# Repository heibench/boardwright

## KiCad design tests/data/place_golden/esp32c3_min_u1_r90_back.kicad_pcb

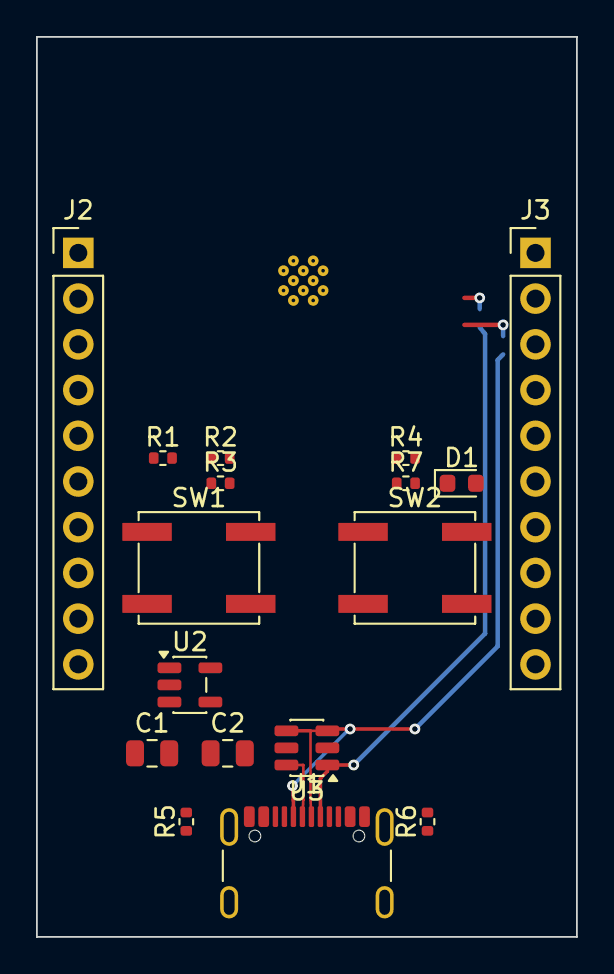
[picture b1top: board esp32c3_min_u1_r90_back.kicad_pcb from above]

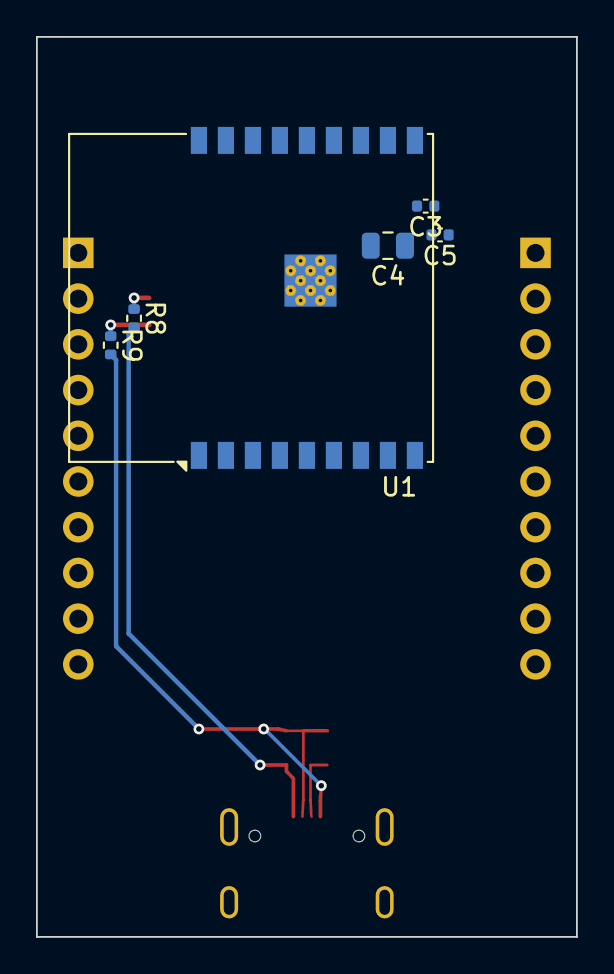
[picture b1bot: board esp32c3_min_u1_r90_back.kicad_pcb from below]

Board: 2 copper layers, 30.0 x 50.0 mm, 23 parts (6 on the bottom side), 24 nets.

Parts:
C1, C2, C4: 10u; C_0805_2012Metric
C3: 100n; C_0402_1005Metric
C5: 1u; C_0402_1005Metric
D1: IO7; LED_0603_1608Metric
J1: USB-C; USB_C_Receptacle_GCT_USB4105-xx-A_16P_TopMnt_Horizontal
J2: LEFT; PinHeader_1x10_P2.54mm_Vertical
J3: RIGHT; PinHeader_1x10_P2.54mm_Vertical
R1, R2, R3, R4: 10k; R_0402_1005Metric
R5, R6: 5.1k; R_0402_1005Metric
R7: 1k; R_0402_1005Metric
R8, R9: 22; R_0402_1005Metric
SW1: BOOT; SW_SPST_EVQP0
SW2: RESET; SW_SPST_EVQP0
U1: ESP32-C3-WROOM-02
U2: AP2112K-3.3; SOT-23-5
U3: USBLC6-2SC6; SOT-23-6

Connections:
+3V3: C2.1, C3.1, C4.1, J2.2, J3.9, R1.1, R2.1, R3.1, R4.1, U1.1, U2.5
CC1: J1.A5, R5.1
CC2: J1.B5, R6.1
EN: C5.1, J2.3, R1.2, SW2.1, U1.2
GND: C1.2, C2.2, C3.2, C4.2, C5.2, D1.1, J1.A1, J1.A12, J1.B1, J1.B12, J1.SH, J2.10, J3.1, J3.10, R5.2, R6.2, SW1.2, SW2.2, U1.9, U1.19, U2.2, U3.2
IO0: J3.2, U1.18
IO1: J3.3, U1.17
IO2: J3.4, R4.2, U1.16
IO3: J3.5, U1.15
IO4: J2.4, U1.3
IO5: J2.5, U1.4
IO6: J2.6, U1.5
IO7: J2.7, R7.1, U1.6
IO8: J2.8, R3.2, U1.7
IO9: J2.9, R2.2, SW1.1, U1.8
IO10: J3.6, U1.10
IO20: J3.7, U1.11
IO21: J3.8, U1.12
LED_A: D1.2, R7.2
USB_DM: J1.A7, J1.B7, R9.2, U3.3, U3.4
USB_DM_M: R9.1, U1.13
USB_DP: J1.A6, J1.B6, R8.2, U3.1, U3.6
USB_DP_M: R8.1, U1.14
VBUS: C1.1, J1.A4, J1.A9, J1.B4, J1.B9, J2.1, U2.1, U2.3, U3.5

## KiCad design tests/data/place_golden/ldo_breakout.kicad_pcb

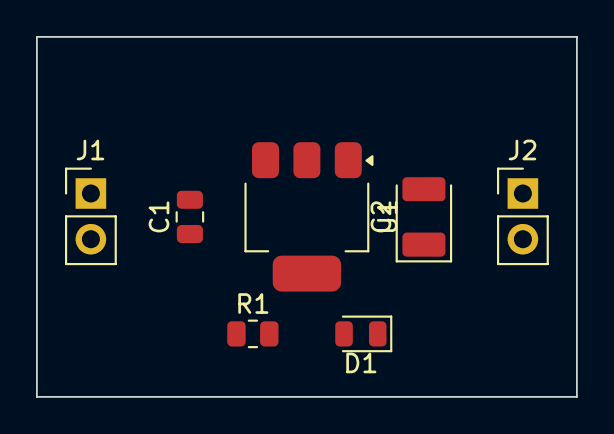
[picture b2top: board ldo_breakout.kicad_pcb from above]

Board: 2 copper layers, 30.0 x 20.0 mm, 7 parts (0 on the bottom side), 4 nets, no tracks yet.

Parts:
C1: 10u; C_0805_2012Metric
C2: 22u tantalum; CP_EIA-3528-21_Kemet-B
D1: green; LED_0805_2012Metric
J1: VIN; PinHeader_1x02_P2.54mm_Vertical
J2: 3V3; PinHeader_1x02_P2.54mm_Vertical
R1: 1k; R_0805_2012Metric
U1: AMS1117-3.3; SOT-223-3_TabPin2

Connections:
+3V3: C2.1, J2.1, R1.1, U1.2
GND: C1.2, C2.2, D1.1, J1.2, J2.2, U1.1
LED_A: D1.2, R1.2
VIN: C1.1, J1.1, U1.3

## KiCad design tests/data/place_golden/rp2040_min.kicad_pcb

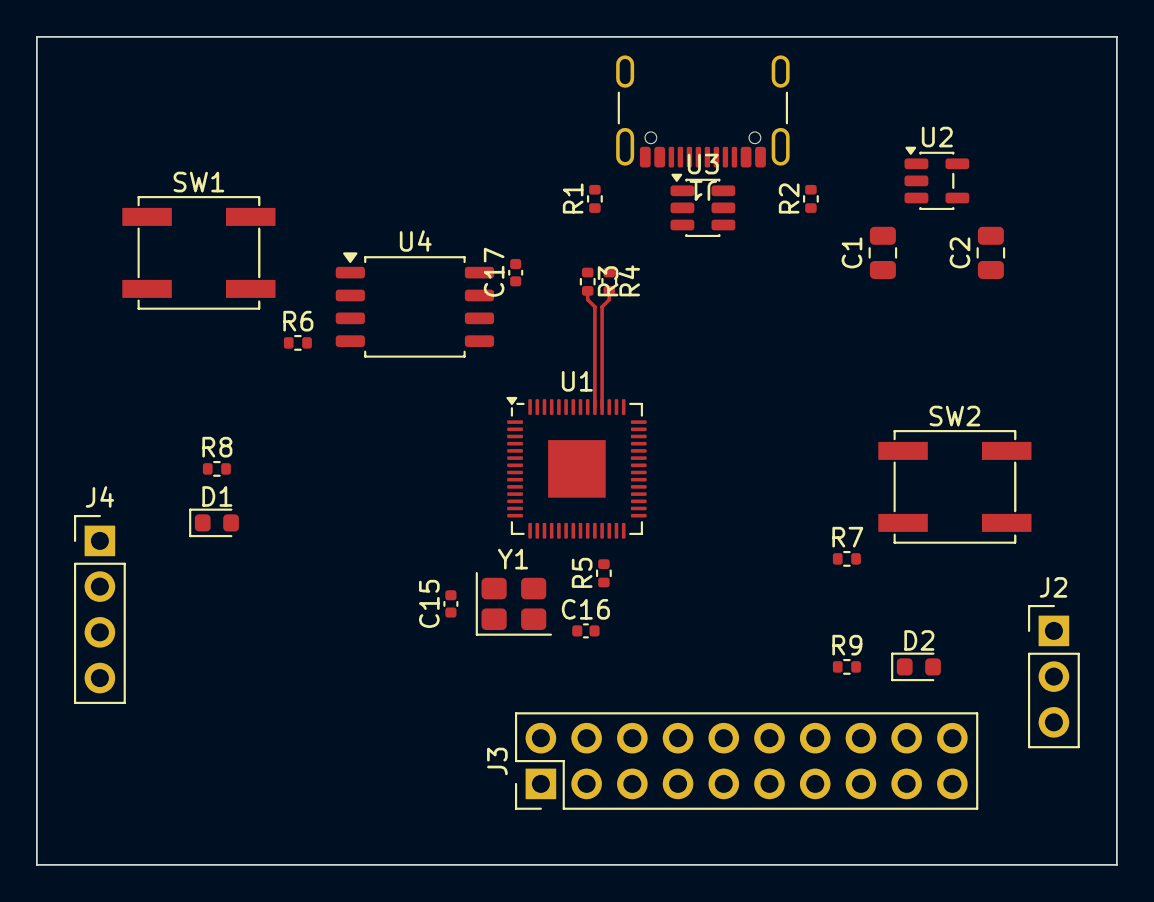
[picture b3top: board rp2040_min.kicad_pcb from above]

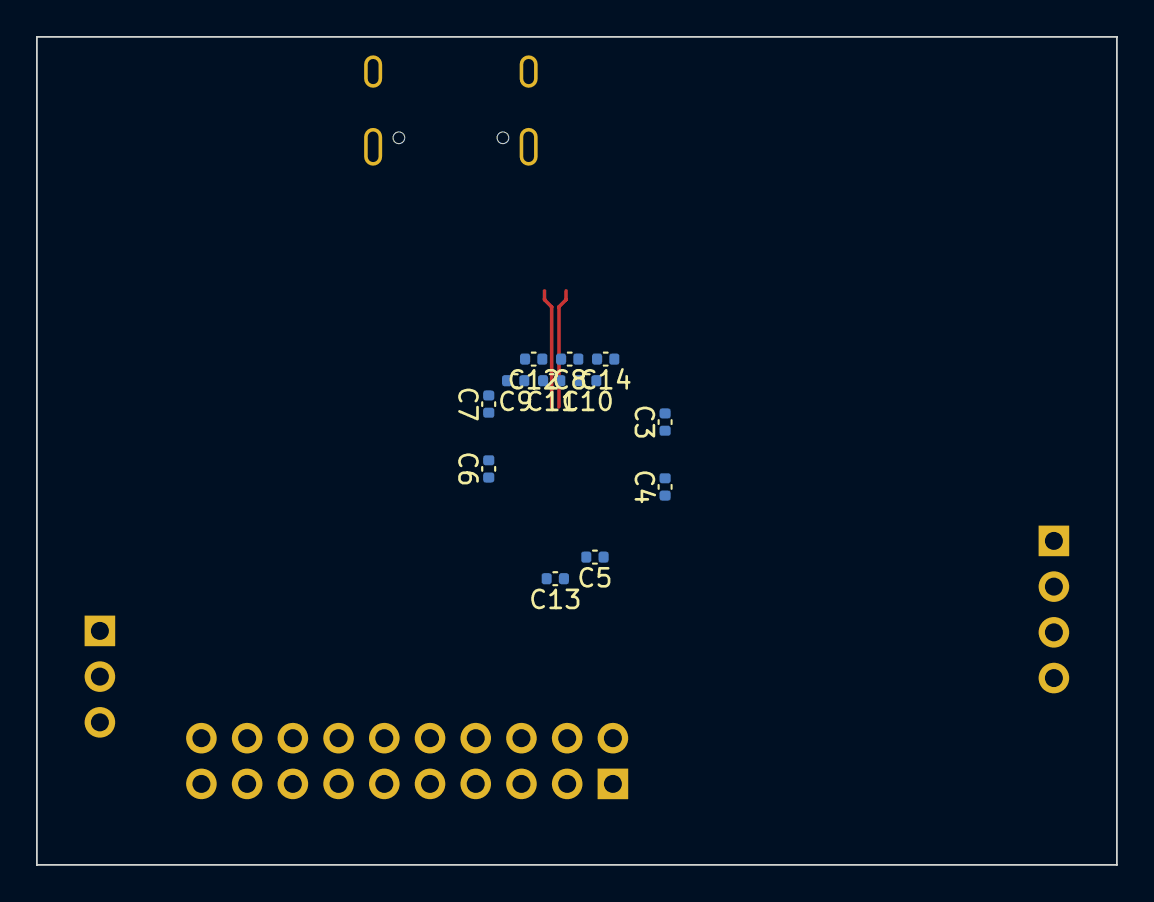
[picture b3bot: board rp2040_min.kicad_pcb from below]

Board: 2 copper layers, 60.0 x 46.0 mm, 39 parts (12 on the bottom side), 46 nets.

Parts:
C1, C2: 10u; C_0805_2012Metric
C3, C4, C5, C6, C7, C8, C9, C10, C13, C14, C17: 100n; C_0402_1005Metric
C11, C12: 1u; C_0402_1005Metric
C15, C16: 15p; C_0402_1005Metric
D1: PWR; LED_0603_1608Metric
D2: GP25; LED_0603_1608Metric
J1: USB-C; USB_C_Receptacle_GCT_USB4105-xx-A_16P_TopMnt_Horizontal
J2: SWD; PinHeader_1x03_P2.54mm_Vertical
J3: GPIO; PinHeader_2x10_P2.54mm_Vertical
J4: PWR; PinHeader_1x04_P2.54mm_Vertical
R1, R2: 5.1k; R_0402_1005Metric
R3, R4: 27; R_0402_1005Metric
R5, R6, R8, R9: 1k; R_0402_1005Metric
R7: 10k; R_0402_1005Metric
SW1: BOOTSEL; SW_SPST_EVQP0
SW2: RESET; SW_SPST_EVQP0
U1: RP2040; QFN-56-1EP_7x7mm_P0.4mm_EP3.2x3.2mm
U2: AP2112K-3.3; SOT-23-5
U3: USBLC6-2SC6; SOT-23-6
U4: W25Q128JVS; SOIC-8_5.3x5.3mm_P1.27mm
Y1: 12MHz; Crystal_SMD_3225-4Pin_3.2x2.5mm

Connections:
+1V1: C12.1, C13.1, C14.1, U1.23, U1.45, U1.50
+3V3: C2.1, C3.1, C4.1, C5.1, C6.1, C7.1, C8.1, C9.1, C10.1, C11.1, C17.1, J4.2, R7.1, R8.1, U1.1, U1.10, U1.22, U1.33, U1.42, U1.43, U1.44, U1.48, U1.49, U2.5, U4.8
BOOT: R6.2, SW1.1
CC1: J1.A5, R1.1
CC2: J1.B5, R2.1
GND: C1.2, C2.2, C3.2, C4.2, C5.2, C6.2, C7.2, C8.2, C9.2, C10.2, C11.2, C12.2, C13.2, C14.2, C15.2, C16.2, C17.2, D1.1, D2.1, J1.A1, J1.A12, J1.B1, J1.B12, J1.SH, J2.2, J4.3, J4.4, R1.2, R2.2, SW1.2, SW2.2, U1.19, U1.57, U2.2, U3.2, U4.4, Y1.2, Y1.4
GPIO0: J3.1, U1.2
GPIO1: J3.2, U1.3
GPIO2: J3.3, U1.4
GPIO3: J3.4, U1.5
GPIO4: J3.5, U1.6
GPIO5: J3.6, U1.7
GPIO6: J3.7, U1.8
GPIO7: J3.8, U1.9
GPIO8: J3.9, U1.11
GPIO9: J3.10, U1.12
GPIO10: J3.11, U1.13
GPIO11: J3.12, U1.14
GPIO12: J3.13, U1.15
GPIO13: J3.14, U1.16
GPIO14: J3.15, U1.17
GPIO15: J3.16, U1.18
GPIO25: R9.1, U1.37
GPIO26: J3.17, U1.38
GPIO27: J3.18, U1.39
GPIO28: J3.19, U1.40
GPIO29: J3.20, U1.41
LED_25: D2.2, R9.2
LED_PWR: D1.2, R8.2
QSPI_SCLK: U1.52, U4.6
QSPI_SD0: U1.53, U4.5
QSPI_SD1: U1.55, U4.2
QSPI_SD2: U1.54, U4.3
QSPI_SD3: U1.51, U4.7
QSPI_SS: R6.1, U1.56, U4.1
RUN: R7.2, SW2.1, U1.26
SWCLK: J2.1, U1.24
SWDIO: J2.3, U1.25
USB_DM: R4.2, U1.46
USB_DM_C: J1.A7, J1.B7, R4.1, U3.3, U3.4
USB_DP: R3.2, U1.47
USB_DP_C: J1.A6, J1.B6, R3.1, U3.1, U3.6
VBUS: C1.1, J1.A4, J1.A9, J1.B4, J1.B9, J4.1, U2.1, U2.3, U3.5
XIN: C15.1, U1.20, Y1.1
XOUT: C16.1, R5.2, Y1.3
XOUT_R: R5.1, U1.21

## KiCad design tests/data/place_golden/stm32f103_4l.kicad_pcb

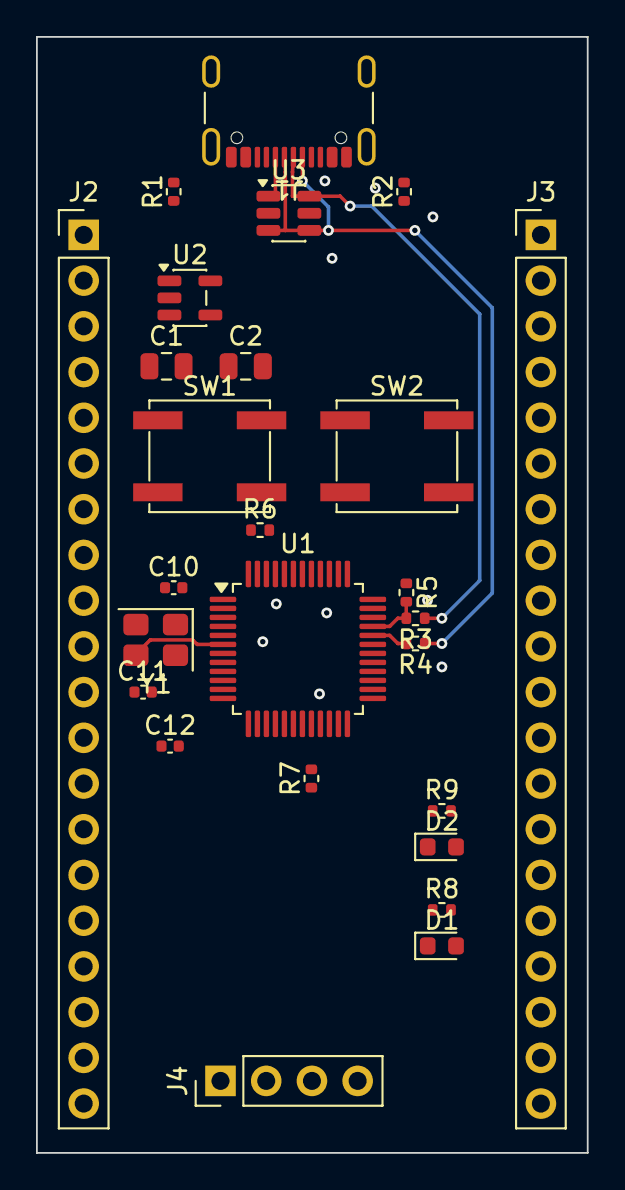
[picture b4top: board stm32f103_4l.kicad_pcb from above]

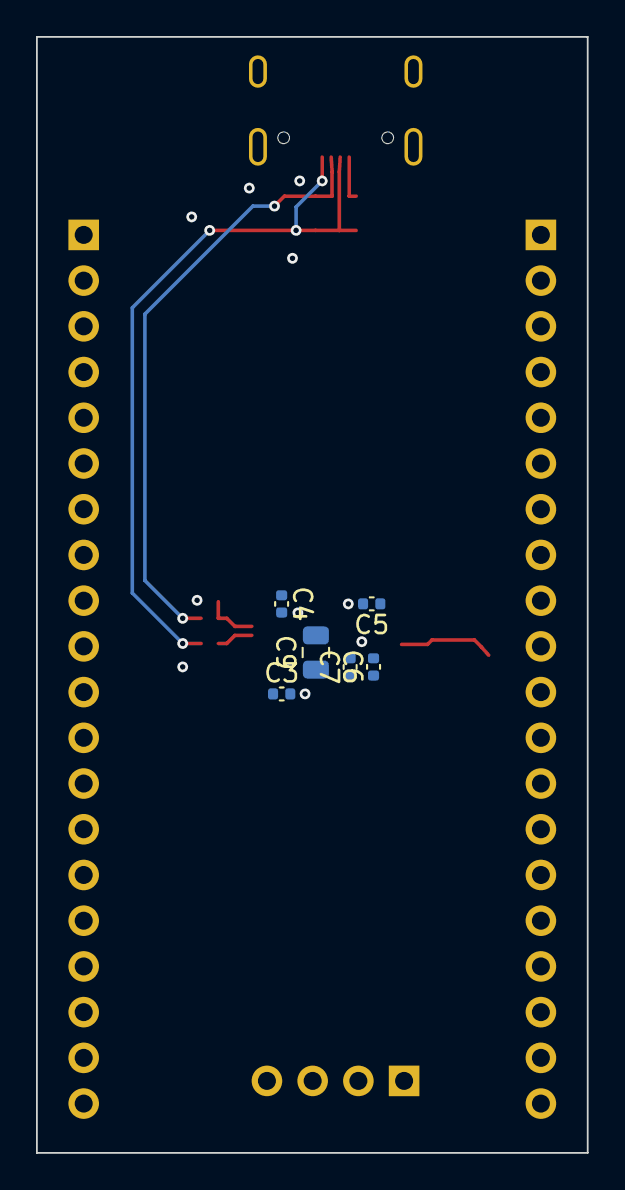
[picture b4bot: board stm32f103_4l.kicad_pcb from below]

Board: 4 copper layers, 30.6 x 62.0 mm, 32 parts (6 on the bottom side), 48 nets.

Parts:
C1, C2: 10u; C_0805_2012Metric
C3, C4, C5, C6, C12: 100n; C_0402_1005Metric
C7: 1u; C_0402_1005Metric
C9: 4.7u; C_0805_2012Metric
C10, C11: 12p; C_0402_1005Metric
D1: PWR; LED_0603_1608Metric
D2: PC13; LED_0603_1608Metric
J1: USB-C; USB_C_Receptacle_GCT_USB4105-xx-A_16P_TopMnt_Horizontal
J2: LEFT; PinHeader_1x20_P2.54mm_Vertical
J3: RIGHT; PinHeader_1x20_P2.54mm_Vertical
J4: SWD; PinHeader_1x04_P2.54mm_Vertical
R1, R2: 5.1k; R_0402_1005Metric
R3, R4: 22; R_0402_1005Metric
R5: 1.5k; R_0402_1005Metric
R6, R7: 10k; R_0402_1005Metric
R8, R9: 1k; R_0402_1005Metric
SW1: BOOT0; SW_SPST_EVQP0
SW2: RESET; SW_SPST_EVQP0
U1: STM32F103C8T6; LQFP-48_7x7mm_P0.5mm
U2: AP2112K-3.3; SOT-23-5
U3: USBLC6-2SC6; SOT-23-6
Y1: 8MHz; Crystal_SMD_3225-4Pin_3.2x2.5mm

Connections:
+3V3: C2.1, C3.1, C4.1, C5.1, C6.1, C7.1, C9.1, J2.1, J2.18, J3.1, J4.1, R5.1, R8.1, R9.1, SW1.2, U1.1, U1.9, U1.24, U1.36, U1.48, U2.5
BOOT0: R6.1, SW1.1, U1.44
BOOT1: R7.1, U1.20
CC1: J1.A5, R1.1
CC2: J1.B5, R2.1
GND: C1.2, C2.2, C3.2, C4.2, C5.2, C6.2, C7.2, C9.2, C10.2, C11.2, C12.2, D1.1, J1.A1, J1.A12, J1.B1, J1.B12, J1.SH, J2.19, J2.20, J3.2, J4.4, R1.2, R2.2, R6.2, R7.2, SW2.2, U1.8, U1.23, U1.35, U1.47, U2.2, U3.2, Y1.2, Y1.4
LED_PWR: D1.2, R8.2
LED_USR: D2.2, R9.2
NRST: C12.1, J2.17, SW2.1, U1.7
OSC_IN: C10.1, U1.5, Y1.1
OSC_OUT: C11.1, U1.6, Y1.3
PA0: J2.5, U1.10
PA1: J2.6, U1.11
PA2: J2.7, U1.12
PA3: J2.8, U1.13
PA4: J2.9, U1.14
PA5: J2.10, U1.15
PA6: J2.11, U1.16
PA7: J2.12, U1.17
PA8: J3.16, U1.29
PA9: J3.15, U1.30
PA10: J3.14, U1.31
PA11: R4.2, U1.32
PA12: R3.2, R5.2, U1.33
PA15: J3.11, U1.38
PB0: J2.13, U1.18
PB1: J2.14, U1.19
PB3: J3.10, U1.39
PB4: J3.9, U1.40
PB5: J3.8, U1.41
PB6: J3.7, U1.42
PB7: J3.6, U1.43
PB8: J3.5, U1.45
PB9: J3.4, U1.46
PB10: J2.15, U1.21
PB11: J2.16, U1.22
PB12: J3.20, U1.25
PB13: J3.19, U1.26
PB14: J3.18, U1.27
PB15: J3.17, U1.28
PC13: D2.1, J2.2, U1.2
PC14: J2.3, U1.3
PC15: J2.4, U1.4
SWCLK: J4.3, U1.37
SWDIO: J4.2, U1.34
USB_DM_C: J1.A7, J1.B7, R4.1, U3.3, U3.4
USB_DP_C: J1.A6, J1.B6, R3.1, U3.1, U3.6
VBUS: C1.1, J1.A4, J1.A9, J1.B4, J1.B9, J3.3, U2.1, U2.3, U3.5

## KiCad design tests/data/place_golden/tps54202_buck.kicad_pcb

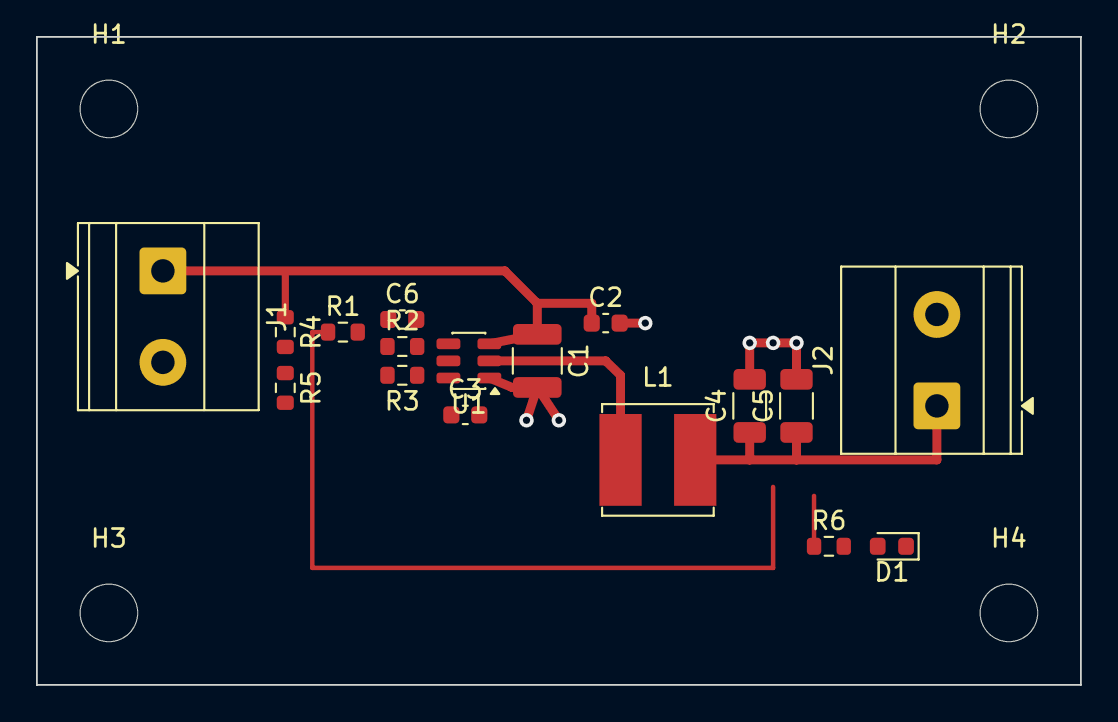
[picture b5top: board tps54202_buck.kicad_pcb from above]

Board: 2 copper layers, 58.0 x 36.0 mm, 21 parts (0 on the bottom side), 9 nets.

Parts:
C1: 10u 35V; C_1210_3225Metric
C2: 100n 50V; C_0603_1608Metric
C3: 100n; C_0603_1608Metric
C4, C5: 22u 16V; C_1206_3216Metric
C6: 75p; C_0603_1608Metric
D1: PWR; LED_0603_1608Metric
H1, H2, H3, H4: M3; MountingHole_3.2mm_M3
J1: VIN 8-28V; TerminalBlock_Phoenix_MKDS-1,5-2-5.08_1x02_P5.08mm_Horizont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
J2: VOUT 5V; TerminalBlock_Phoenix_MKDS-1,5-2-5.08_1x02_P5.08mm_Horizont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
L1: 15u 3A; L_Bourns_SRN6045TA
R1: 49.9; R_0603_1608Metric
R2: 100k; R_0603_1608Metric
R3: 13.3k; R_0603_1608Metric
R4: 511k; R_0603_1608Metric
R5: 105k; R_0603_1608Metric
R6: 2.2k; R_0603_1608Metric
U1: TPS54202; SOT-23-6

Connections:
BOOT: C3.1, U1.6
EN: R4.2, R5.1, U1.5
FB: C6.2, R2.2, R3.1, U1.4
GND: C1.2, C2.2, C4.2, C5.2, D1.1, J1.2, J2.2, R3.2, R5.2, U1.1
LED_A: D1.2, R6.2
SW: C3.2, L1.1, U1.2
VIN: C1.1, C2.1, J1.1, R4.1, U1.3
VOUT: C4.1, C5.1, J2.1, L1.2, R1.1, R6.1
VSENSE: C6.1, R1.2, R2.1
